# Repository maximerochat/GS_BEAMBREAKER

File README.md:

# GS_BEAMBREAKER
This project is a first iteration of 2.4GHz FSK signal beam steering

I'll try do document this project along it's advancement.

# Table of content
- [Basic ideas and calculation](docs/basic_calculations.md)
- [Hardware](docs/hardware.md)
- [Antenna Design](docs/antenna_design.md)
- ...

# Goal of this project 
I'm not a professional RF designer, just an enthusiastic Computer Science student trying to understand the complexity of beam forming. Since I had trouble finding guide about basic beam forming hardware and software, I'm trying to produce good material for future person like me. If you are interested in collaborating or want to correct me and point out mistakes I'm made, feel free to contact me or to raise issues.

# Notice
I am currently only working on the physics and thinking of the project, I'll try do documentate everything along my research. This means that the current hardware template is not accurate, it's juste a basic implementation of a SX1280 radio (I didn't tested it for the moment, I'm about to produce it in a few weeks). The hardware for this project I hope will be built during the next academic semester, I'll try to contact some labs in my university (EPFL) to see if they can help me in my jounrey

# Ressources
- bible of phased array : http://twanclik.free.fr/electricity/electronic/pdfdone11/Phased.Array.Antenna.Handbook.Artech.House.Publishers.Second.Edition.eBook-kB.pdf
- square patch antenna design : https://www.researchgate.net/publication/319176011_Design_Analysis_of_Square_Microstrip_Patch_Antenna
- basic interference pattern model : https://www.claytex.com/blog/modelling-of-phased-array-antenna/
- courses about phased array : https://zinka.wordpress.com/material/
- Antenna design :
  - https://www.researchgate.net/publication/292508017_Design_of_microstrip_antenna_for_wireless_communication_at_24_GHZ
  - calculator : https://resources.altium.com/fr/p/microstrip-patch-antenna-calculator-rf-designers

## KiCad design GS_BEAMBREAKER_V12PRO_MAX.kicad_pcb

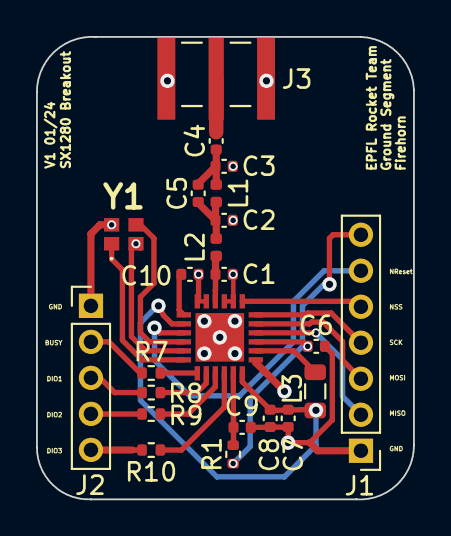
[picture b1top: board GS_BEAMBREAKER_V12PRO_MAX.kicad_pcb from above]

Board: 2 copper layers, 20.9 x 25.7 mm, 23 parts (0 on the bottom side), 25 nets.

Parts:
C1: 0.8pF; C_0402_1005Metric
C2, C3: 1.2pF; C_0402_1005Metric
C4: 100pF; C_0402_1005Metric
C5: 0.5pF; C_0402_1005Metric
C6, C9: 100nF; C_0402_1005Metric
C7: 470nF; C_0402_1005Metric
C8, C10: 10nF; C_0402_1005Metric
J1: Conn_01x07_Pin; PinHeader_1x07_P2.00mm_Vertical
J2: Conn_01x05_Pin; PinHeader_1x05_P2.00mm_Vertical
J3: EMPCB.SMAFSTJ.B.HT; TAOGLAS_EMPCB.SMAFSTJ.B.HT
L1: 2.5nH; L_0402_1005Metric
L2: 3nH; L_0402_1005Metric
L3: 15uH; L_0805_2012Metric
R1: 0; R_0402_1005Metric
R7, R8, R9, R10: 33; R_0402_1005Metric
SX1280-2: SX1280
Y1: NX2016SA-26M-STD-CZS-1; NX2016SA26MSTDCZS1

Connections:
/BUSY: R7.2, SX1280-2.7 (BUSY)
/DIO1: R8.2, SX1280-2.8 (DIO1)
/DIO2: R9.2, SX1280-2.9 (DIO2)
/DIO3: R10.2, SX1280-2.10 (DIO3)
/MISO_TX: J1.2, SX1280-2.16 (MISO_TX)
/MOSI_RX: J1.3, SX1280-2.17 (MOSI_RX)
/NRESET: J1.6, SX1280-2.3 (NRESET)
/NSS_CTS: J1.5, SX1280-2.19 (NSS_CTS)
/SCK: J1.4, SX1280-2.18 (SCK_RTSN)
/VDD_RADIO: C6.1, J1.7, R1.1, SX1280-2.15 (VBAT)
/V_DCC: C7.1, C8.1, L3.1, SX1280-2.2 (VDD_IN), SX1280-2.12 (DCC_FB)
/V_DCC2: L3.2, SX1280-2.14 (DCC_SW)
/V_PA: C10.1, SX1280-2.1 (VR_PA)
/XTA: SX1280-2.4 (XTA), Y1.3 (CRYSTAL_2)
GND: C1.2, C2.2, C3.2, C6.2, C7.2, C8.2, C9.2, C10.2, J1.1, J2.1, J3.SH1, SX1280-2.0 (GND), SX1280-2.5 (GND), SX1280-2.13 (GND), SX1280-2.20 (GND), SX1280-2.21 (GND), SX1280-2.23 (GND), SX1280-2.24 (GND), Y1.2 (GND_1), Y1.4 (GND_2)
unnamed: C2.1, C5.1, L1.1, L2.2
unnamed: C3.1, C4.1, C5.2, L1.2
unnamed: C4.2, J3.1
unnamed: J2.2, R7.1
unnamed: J2.3, R8.1
unnamed: J2.4, R9.1
unnamed: J2.5, R10.1
unnamed: C1.1, L2.1, SX1280-2.22 (RFIO)
unnamed: C9.1, R1.2, SX1280-2.11 (VBAT_IO)
unnamed: SX1280-2.6 (XTB), Y1.1 (CRYSTAL_1)

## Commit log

2024-01-15 modified project structure + added start of documentation structure
2024-01-15 doc change + hardware project structure
2024-01-15 change continues
2024-01-15 added some component reference
2024-01-16 antenna doc start
2024-01-16 doc update
2024-01-26 Update README.md with a short notice on the project current state
